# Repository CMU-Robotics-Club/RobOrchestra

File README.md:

RobOrchestra
=============

Welcome to RobOrchestra! RobOrchestra is an ongoing project in the Carnegie Mellon Robotics Club that aims to explore the creative possibilities for robotic instruments. We design, build and program robots that read music from MIDI data in order to put on musical performances. Our goal is to create a full robotic orchestra that is able to play from arrangements from standard MIDI files, and is also able to "improvise" unique polyphonic music in real time based off of music generation algorithms developed by our team.

Check out this demo video: https://drive.google.com/open?id=1UAF38HtQlL7tU6Xmdl4eHLXhHpyFQM5X

### How it works.
	
The robots, all powered by Arduinos with MIDI shields, operate via a distributed network. A laptop acts as the "conductor", transmitting MIDI siginals through the network of robots. Each robot reads the data and picks out its own part, and then plays it accordingly. We use Processing, a powerful music programming language, to control the orchestra, however it should work with nearly any MIDI software.

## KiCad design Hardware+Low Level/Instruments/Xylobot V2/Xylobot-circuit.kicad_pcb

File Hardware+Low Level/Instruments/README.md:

Instruments
===========

Each directory contains Arduino code, CAD files and documentation for each of our Robotic Instruments.

### Completed Robots
* tomBot
* snareBot
* xyloBot

### In Progress Robots
* ukuleleBot
* roboOboe
* harmonicaBot
* ViolinBot
* XyloBot V2

(Older, unused robot designs can be found in the "archives" directory.)

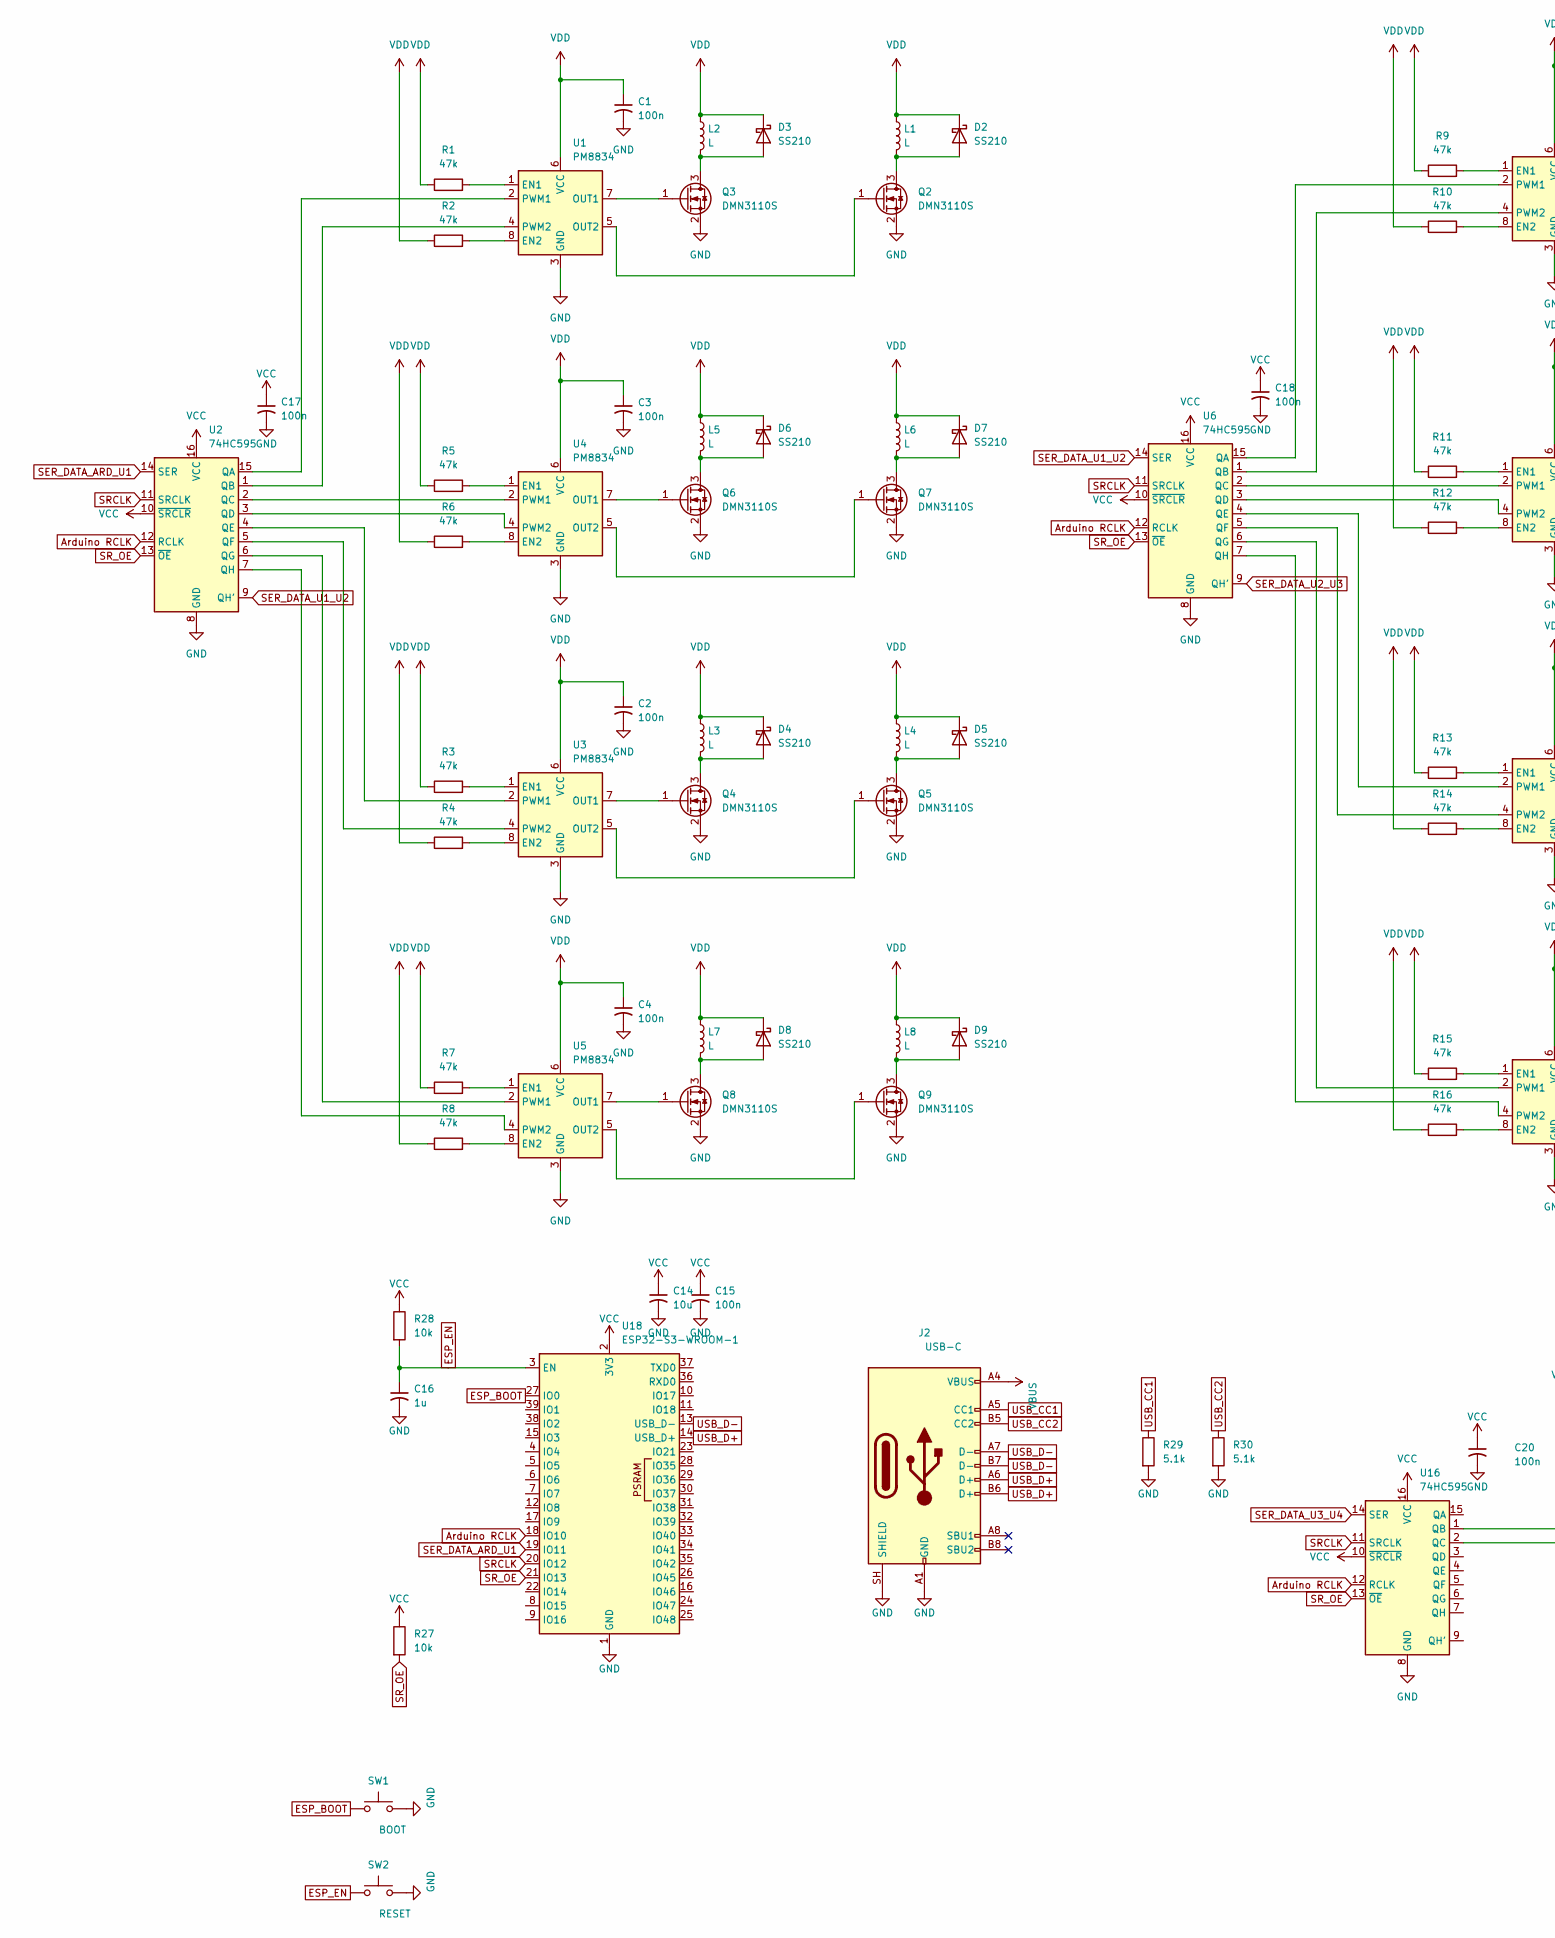
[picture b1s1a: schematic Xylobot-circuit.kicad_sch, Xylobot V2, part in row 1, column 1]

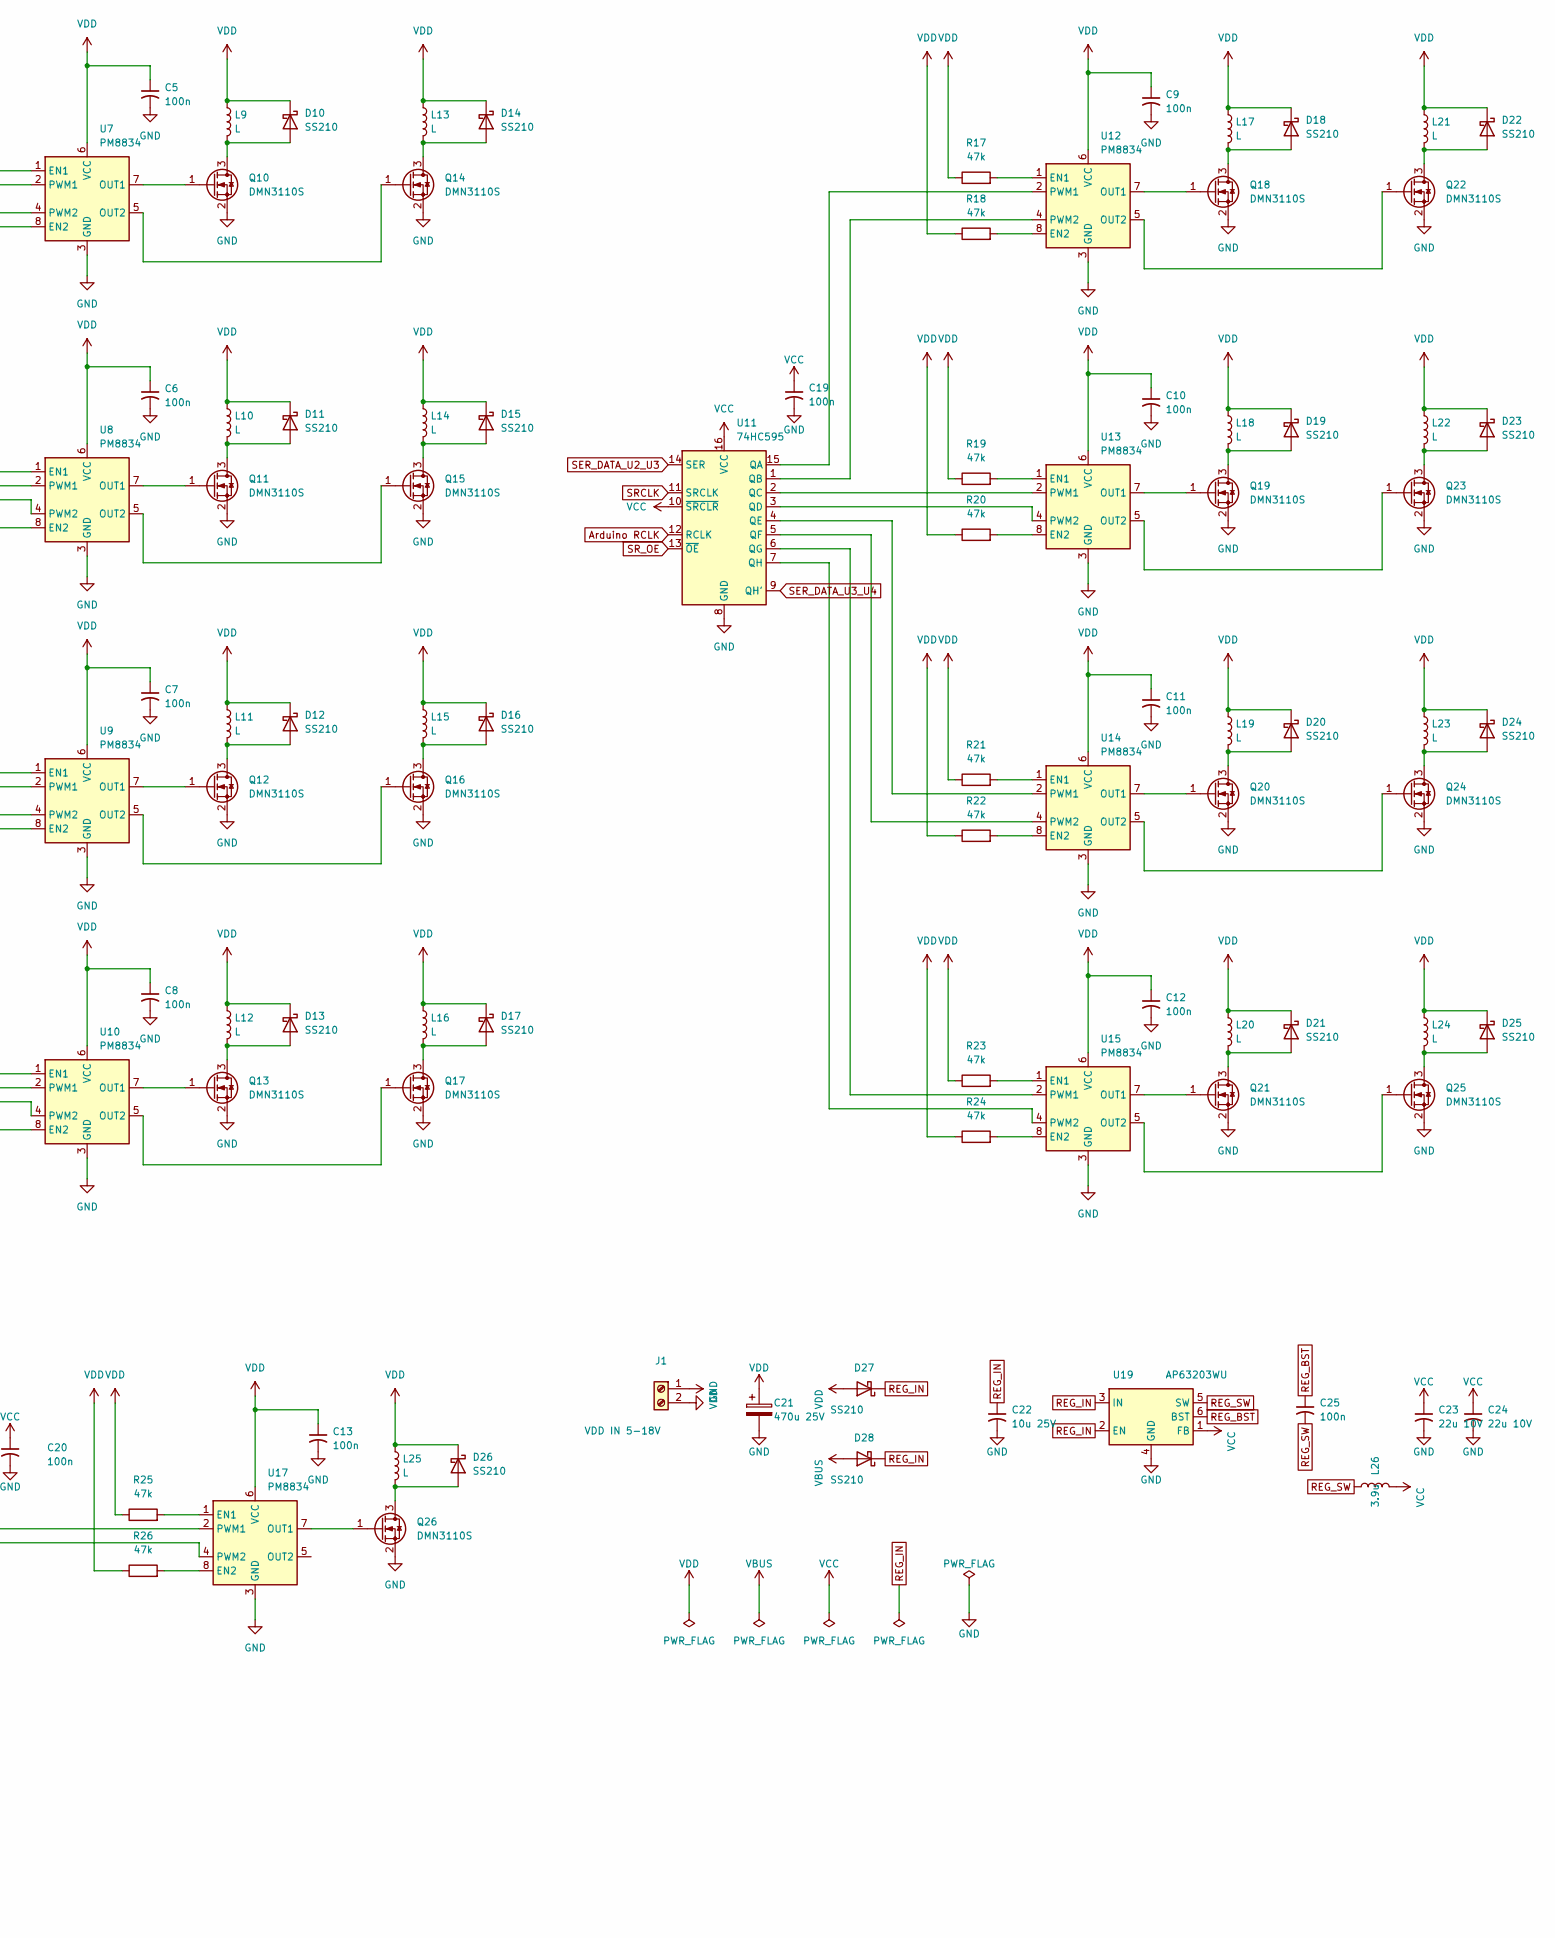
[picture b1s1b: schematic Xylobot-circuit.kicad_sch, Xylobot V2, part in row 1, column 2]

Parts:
C1, C2, C3, C4, C5, C6, C7, C8, C9, C10, C11, C12, C13, C15, C17, C18, C19, C20, C25: 100n; C_0603_1608Metric
C14: 10u; C_0805_2012Metric
C16: 1u; C_0603_1608Metric
C21: 470u 25V; CP_Radial_D10.0mm_P5.00mm
C22: 10u 25V; C_1206_3216Metric
C23, C24: 22u 10V; C_0805_2012Metric
D2, D3, D4, D5, D6, D7, D8, D9, D10, D11, D12, D13, D14, D15, D16, D17, D18, D19, D20, D21, D22, D23, D24, D25, D26, D27, D28: SS210; D_SMA
J1: VDD IN 5-18V; TerminalBlock_Phoenix_MKDS-1,5-2-5.08_1x02_P5.08mm_Horizont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
J2: USB-C; USB_C_Receptacle_HRO_TYPE-C-31-M-12
L1, L2, L3, L4, L5, L6, L7, L8, L9, L10, L11, L12, L13, L14, L15, L16, L17, L18, L19, L20, L21, L22, L23, L24, L25: L; TerminalBlock_Phoenix_MKDS-1,5-2-5.08_1x02_P5.08mm_Horizont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
L26: 3.9u; L_Bourns-SRN4018
Q2, Q3, Q4, Q5, Q6, Q7, Q8, Q9, Q10, Q11, Q12, Q13, Q14, Q15, Q16, Q17, Q18, Q19, Q20, Q21, Q22, Q23, Q24, Q25, Q26: DMN3110S; SOT-23
R1, R2, R3, R4, R5, R6, R7, R8, R9, R10, R11, R12, R13, R14, R15, R16, R17, R18, R19, R20, R21, R22, R23, R24, R25, R26: 47k; R_0603_1608Metric
R27, R28: 10k; R_0603_1608Metric
R29, R30: 5.1k; R_0603_1608Metric
SW1: BOOT; SW_PUSH_6mm
SW2: RESET; SW_PUSH_6mm
U1, U3, U4, U5, U7, U8, U9, U10, U12, U13, U14, U15, U17: PM8834; SOIC-8_3.9x4.9mm_P1.27mm
U2, U6, U11, U16: 74HC595; SOIC-16_3.9x9.9mm_P1.27mm
U18: ESP32-S3-WROOM-1
U19: AP63203WU; TSOT-23-6

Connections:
Arduino RCLK: U2.12 (RCLK), U6.12 (RCLK), U11.12 (RCLK), U16.12 (RCLK), U18.18 (IO10)
GND: C1.2, C2.2, C3.2, C4.2, C5.2, C6.2, C7.2, C8.2, C9.2, C10.2, C11.2, C12.2, C13.2, C14.2, C15.2, C16.2, C17.2, C18.2, C19.2, C20.2, C21.2, C22.2, C23.2, C24.2, J1.2, J2.A1 (GND), J2.A12 (GND), J2.B1 (GND), J2.B12 (GND), J2.SH (SHIELD), Q2.2 (S), Q3.2 (S), Q4.2 (S), Q5.2 (S), Q6.2 (S), Q7.2 (S), Q8.2 (S), Q9.2 (S), Q10.2 (S), Q11.2 (S), Q12.2 (S), Q13.2 (S), Q14.2 (S), Q15.2 (S), Q16.2 (S), Q17.2 (S), Q18.2 (S), Q19.2 (S), Q20.2 (S), Q21.2 (S), Q22.2 (S), Q23.2 (S), Q24.2 (S), Q25.2 (S), Q26.2 (S), R29.2, R30.2, SW1.2, SW2.2, U1.3 (GND), U2.8 (GND), U3.3 (GND), U4.3 (GND), U5.3 (GND), U6.8 (GND), U7.3 (GND), U8.3 (GND), U9.3 (GND), U10.3 (GND), U11.8 (GND), U12.3 (GND), U13.3 (GND), U14.3 (GND), U15.3 (GND), U16.8 (GND), U17.3 (GND), U18.1 (GND), U18.40 (GND), U18.41 (GND), U19.4 (GND)
unnamed: C22.1, D27.1 (K), D28.1 (K), U19.2 (EN), U19.3 (IN)
unnamed: C25.1, U19.6 (BST)
unnamed: C25.2, L26.1, U19.5 (SW)
unnamed: D2.2 (A), L1.2, Q2.3 (D)
unnamed: D3.2 (A), L2.2, Q3.3 (D)
unnamed: D4.2 (A), L3.2, Q4.3 (D)
unnamed: D5.2 (A), L4.2, Q5.3 (D)
unnamed: D6.2 (A), L5.2, Q6.3 (D)
unnamed: D7.2 (A), L6.2, Q7.3 (D)
unnamed: D8.2 (A), L7.2, Q8.3 (D)
unnamed: D9.2 (A), L8.2, Q9.3 (D)
unnamed: D10.2 (A), L9.2, Q10.3 (D)
unnamed: D11.2 (A), L10.2, Q11.3 (D)
unnamed: D12.2 (A), L11.2, Q12.3 (D)
unnamed: D13.2 (A), L12.2, Q13.3 (D)
unnamed: D14.2 (A), L13.2, Q14.3 (D)
unnamed: D15.2 (A), L14.2, Q15.3 (D)
unnamed: D16.2 (A), L15.2, Q16.3 (D)
unnamed: D17.2 (A), L16.2, Q17.3 (D)
unnamed: D18.2 (A), L17.2, Q18.3 (D)
unnamed: D19.2 (A), L18.2, Q19.3 (D)
unnamed: D20.2 (A), L19.2, Q20.3 (D)
unnamed: D21.2 (A), L20.2, Q21.3 (D)
unnamed: D22.2 (A), L21.2, Q22.3 (D)
unnamed: D23.2 (A), L22.2, Q23.3 (D)
unnamed: D24.2 (A), L23.2, Q24.3 (D)
unnamed: D25.2 (A), L24.2, Q25.3 (D)
unnamed: D26.2 (A), L25.2, Q26.3 (D)
unnamed: D28.2 (A), J2.A4 (VBUS), J2.A9 (VBUS), J2.B4 (VBUS), J2.B9 (VBUS)
unnamed: J2.A5 (CC1), R29.1
unnamed: J2.A6 (D+), J2.B6 (D+), U18.14 (USB_D+)
unnamed: J2.A7 (D-), J2.B7 (D-), U18.13 (USB_D-)
unnamed: J2.B5 (CC2), R30.1
unnamed: Q2.1 (G), U1.5 (OUT2)
unnamed: Q3.1 (G), U1.7 (OUT1)
unnamed: Q4.1 (G), U3.7 (OUT1)
unnamed: Q5.1 (G), U3.5 (OUT2)
unnamed: Q6.1 (G), U4.7 (OUT1)
unnamed: Q7.1 (G), U4.5 (OUT2)
unnamed: Q8.1 (G), U5.7 (OUT1)
unnamed: Q9.1 (G), U5.5 (OUT2)
unnamed: Q10.1 (G), U7.7 (OUT1)
unnamed: Q11.1 (G), U8.7 (OUT1)
unnamed: Q12.1 (G), U9.7 (OUT1)
unnamed: Q13.1 (G), U10.7 (OUT1)
unnamed: Q14.1 (G), U7.5 (OUT2)
unnamed: Q15.1 (G), U8.5 (OUT2)
unnamed: Q16.1 (G), U9.5 (OUT2)
unnamed: Q17.1 (G), U10.5 (OUT2)
unnamed: Q18.1 (G), U12.7 (OUT1)
unnamed: Q19.1 (G), U13.7 (OUT1)
unnamed: Q20.1 (G), U14.7 (OUT1)
unnamed: Q21.1 (G), U15.7 (OUT1)
unnamed: Q22.1 (G), U12.5 (OUT2)
unnamed: Q23.1 (G), U13.5 (OUT2)
unnamed: Q24.1 (G), U14.5 (OUT2)
unnamed: Q25.1 (G), U15.5 (OUT2)
unnamed: Q26.1 (G), U17.7 (OUT1)
unnamed: SW1.1, U18.27 (IO0)
unnamed: R1.2, U1.1 (EN1)
unnamed: R2.2, U1.8 (EN2)
unnamed: U1.2 (PWM1), U2.15 (QA)
unnamed: U1.4 (PWM2), U2.1 (QB)
unnamed: U2.2 (QC), U4.2 (PWM1)
unnamed: U2.3 (QD), U4.4 (PWM2)
unnamed: U2.4 (QE), U3.2 (PWM1)
unnamed: U2.5 (QF), U3.4 (PWM2)
unnamed: U2.6 (QG), U5.2 (PWM1)
unnamed: U2.7 (QH), U5.4 (PWM2)
unnamed: R3.2, U3.1 (EN1)
unnamed: R4.2, U3.8 (EN2)
unnamed: R5.2, U4.1 (EN1)
unnamed: R6.2, U4.8 (EN2)
unnamed: R7.2, U5.1 (EN1)
unnamed: R8.2, U5.8 (EN2)
unnamed: U6.15 (QA), U7.2 (PWM1)
unnamed: U6.1 (QB), U7.4 (PWM2)
unnamed: U6.2 (QC), U8.2 (PWM1)
unnamed: U6.3 (QD), U8.4 (PWM2)
unnamed: U6.4 (QE), U9.2 (PWM1)
unnamed: U6.5 (QF), U9.4 (PWM2)
unnamed: R9.2, U7.1 (EN1)
unnamed: R10.2, U7.8 (EN2)
unnamed: R11.2, U8.1 (EN1)
unnamed: R12.2, U8.8 (EN2)
unnamed: R13.2, U9.1 (EN1)
unnamed: R14.2, U9.8 (EN2)
unnamed: R15.2, U10.1 (EN1)
unnamed: R16.2, U10.8 (EN2)
unnamed: U6.6 (QG), U10.2 (PWM1)
unnamed: U6.7 (QH), U10.4 (PWM2)
unnamed: U11.15 (QA), U12.2 (PWM1)
unnamed: U11.1 (QB), U12.4 (PWM2)
unnamed: U11.2 (QC), U13.2 (PWM1)
unnamed: U11.3 (QD), U13.4 (PWM2)
unnamed: U11.4 (QE), U14.2 (PWM1)
unnamed: U11.5 (QF), U14.4 (PWM2)
unnamed: U11.6 (QG), U15.2 (PWM1)
unnamed: U11.7 (QH), U15.4 (PWM2)
unnamed: R17.2, U12.1 (EN1)
unnamed: R18.2, U12.8 (EN2)
unnamed: R19.2, U13.1 (EN1)
unnamed: R20.2, U13.8 (EN2)
unnamed: R21.2, U14.1 (EN1)
unnamed: R22.2, U14.8 (EN2)
unnamed: R23.2, U15.1 (EN1)
unnamed: R24.2, U15.8 (EN2)
unnamed: U16.1 (QB), U17.2 (PWM1)
unnamed: U16.2 (QC), U17.4 (PWM2)
unnamed: R25.2, U17.1 (EN1)
unnamed: R26.2, U17.8 (EN2)
unnamed: C16.1, R28.2, SW2.1, U18.3 (EN)
SER_DATA_ARD_U1: U2.14 (SER), U18.19 (IO11)
SER_DATA_U1_U2: U2.9 (QH'), U6.14 (SER)
SER_DATA_U2_U3: U6.9 (QH'), U11.14 (SER)
SER_DATA_U3_U4: U11.9 (QH'), U16.14 (SER)
SRCLK: U2.11 (SRCLK), U6.11 (SRCLK), U11.11 (SRCLK), U16.11 (SRCLK), U18.20 (IO12)
SR_OE: R27.2, U2.13 (~OE), U6.13 (~OE), U11.13 (~OE), U16.13 (~OE), U18.21 (IO13)
VCC: C14.1, C15.1, C17.1, C18.1, C19.1, C20.1, C23.1, C24.1, L26.2, R27.1, R28.1, U2.10 (~SRCLR), U2.16 (VCC), U6.10 (~SRCLR), U6.16 (VCC), U11.10 (~SRCLR), U11.16 (VCC), U16.10 (~SRCLR), U16.16 (VCC), U18.2 (3V3), U19.1 (FB)
VDD: C1.1, C2.1, C3.1, C4.1, C5.1, C6.1, C7.1, C8.1, C9.1, C10.1, C11.1, C12.1, C13.1, C21.1, D2.1 (K), D3.1 (K), D4.1 (K), D5.1 (K), D6.1 (K), D7.1 (K), D8.1 (K), D9.1 (K), D10.1 (K), D11.1 (K), D12.1 (K), D13.1 (K), D14.1 (K), D15.1 (K), D16.1 (K), D17.1 (K), D18.1 (K), D19.1 (K), D20.1 (K), D21.1 (K), D22.1 (K), D23.1 (K), D24.1 (K), D25.1 (K), D26.1 (K), D27.2 (A), J1.1, L1.1, L2.1, L3.1, L4.1, L5.1, L6.1, L7.1, L8.1, L9.1, L10.1, L11.1, L12.1, L13.1, L14.1, L15.1, L16.1, L17.1, L18.1, L19.1, L20.1, L21.1, L22.1, L23.1, L24.1, L25.1, R1.1, R2.1, R3.1, R4.1, R5.1, R6.1, R7.1, R8.1, R9.1, R10.1, R11.1, R12.1, R13.1, R14.1, R15.1, R16.1, R17.1, R18.1, R19.1, R20.1, R21.1, R22.1, R23.1, R24.1, R25.1, R26.1, U1.6 (VCC), U3.6 (VCC), U4.6 (VCC), U5.6 (VCC), U7.6 (VCC), U8.6 (VCC), U9.6 (VCC), U10.6 (VCC), U12.6 (VCC), U13.6 (VCC), U14.6 (VCC), U15.6 (VCC), U17.6 (VCC)

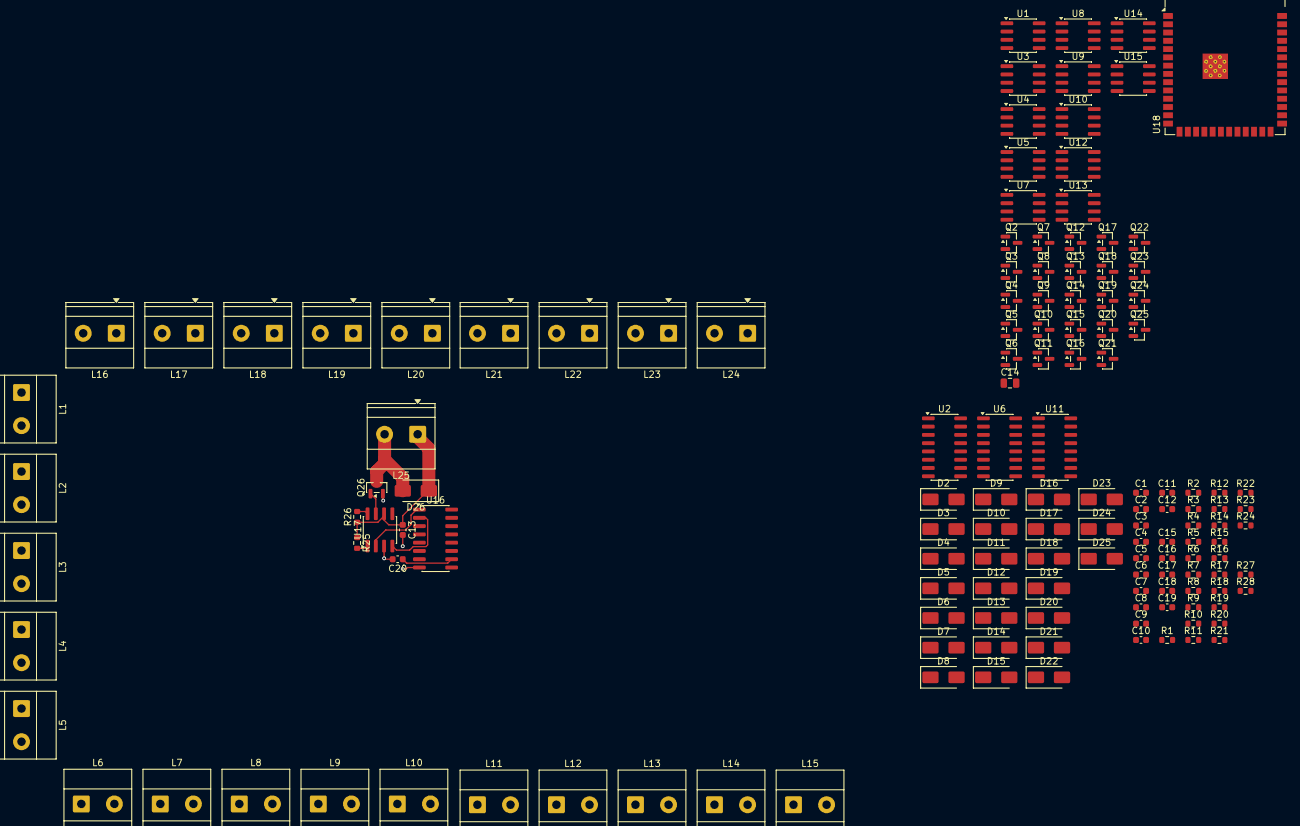
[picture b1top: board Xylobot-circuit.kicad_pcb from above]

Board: 2 copper layers, 141 parts (0 on the bottom side), 113 nets.

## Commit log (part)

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2017-11-13 Removed Redundant Notes
    There were redundant notes. They are now gone. Celebrate!
2017-11-13 Rhythm Updates
2017-11-13 BASIC MARKOV DOESNT COMPILE - TEMPORARY MAJOR CHANGES
    Changes are modifying all of basic markov, chorddetection, and playnotethread to take int arrays
2017-11-27 Removed unnecessary files in BasicMarkov
2017-11-27 Partially implemented proper chord playing in PlayNoteThread
2017-11-27 Fixed some flaws in chord detection with making assumptions based on order of notes inputted
2017-11-28 Made Chord Detection slightly more accurate when returning basic major and minor chords
2017-12-18 Messing around with having chords gradually decrescendo and jump back up to full volume occasionally, rather than just playing 10% of the chords chosen randomly. Seems okay to me (less like monkey ba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
2018-01-22 Updated slider range on interactive demo
2018-01-22 Actually committing the dominant 7th fix...
2018-01-29 Cleaned up xylobot low level. To do: Discretize time and teach the low-level code to go back in time on receiving MIDI messages.
2018-02-19 Updated xylobot code, moved BasicMarkov from Test Code to Music Generation Algorithms, renamed it ChordMarkov.
2018-02-19 Old Xylobot code retrieved, new Xylobot code cleaned up
2018-03-05 Updated pin numbers in Arduino Xylobot code
2018-03-05 Xylobot code now timing each solenoid independently. All chords now not simultaneous, but the time discrepancies are smaller. Might be an improvement? Still need to clean up unused code though...
2018-03-19 Made the state length its own variable in the Markov chain code.
2018-03-19 Got the Ukelele Arduino code to compile (I hope it's the right file, and I'm pretty sure it compiles now and didn't before), but I'm not great with C, so I'm not sure it works at all. A good chunk of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
2018-03-26 Updated snarebot code
2018-03-26 CounterPointFirstSpecies and Generate added to CounterPointFirstSpecies Folder
2018-03-26 Added RULEFILTER and CHORDGETTER functions
2018-04-02 Add files via upload
    Made interactive demo melody more linear.
2018-04-02 Tested bassLineGen and added Voice class (not sure if we will use this or not but we'll see lol)
2018-04-09 Add files via upload
    Added second line
2018-04-09 More playign with the score stuff. More comments.
2018-04-09 Added score to Generate
2018-04-09 NAIVE MELODY LINE
2018-04-16 Revert "Changed solenoid pin numbers. Code not compiling; something about arrays not being correct..."
    This reverts commit 65ad4aaf9797b1c8c7a006cf14857be444ede811.
2018-04-16 Pins should hopefully be correct?
2018-04-16 Removed the other Ukelelebot code file
2018-04-16 Add files via upload
    Added melody and harmony button labels
2018-04-16 fixed everything
2018-04-23 Added second species file and fixed resolution of first species outputted score
2018-04-30 Ukelele code changes
2018-10-29 Changed OpenCV folder to Interaction
2018-11-01 Added HSVColorTracking Example from OpenCV Library
    So Processing's version of OpenCV is really old. We don't have fast circle tracking algorithms like Hough Circle Transform. Instead we'll have to either track color, blobs, or cascades. I found an ex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
2018-11-05 Put HSV stuff in CV_Interaction
2018-11-12 magnitude
    added double get_magnitude to point vector class
2018-11-19 Added more accuracy to opencv
2018-11-26 Added Ukulele test code
2019-01-25 Various changes. Got ChordMarkov to play Despacito
2019-01-25 Revert "no message"
    This reverts commit c9e763ef3822c5faf165526e0a1690b5cc227487.
2019-01-28 Finished resolving merge conflicts. Hopefully stuff still works; if not, revert.
2019-02-13 Uploaded in-progress CAD parts to github
2019-02-19 Messed around with Markov_with_CV; still not picking up the object correctly.
2019-02-25 Moved blur before display so when we grab a color, we grab the blurred color. Then lowered thresholds to filter more background noise.
2019-02-28 Folder Reordering
    Cleaned up the repo. Still contains file repetitions, but should be more organized now.
2019-03-01 Added SimpleSynth 64-bit port
    SimpleSynth hasn't been updated since 2009, and we probably want to keep using it. Recompiled the source code for macOS 10.14 and fixed MOST deprecation issues. Still not a 100% future proof, but sho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
    P.S. I checked and we are permitted to distribute copies of the program (read: about simplesynth, in app).
2019-03-28 Xylobot code cleanup. Should work (tested on RoboOboe, plus partial testing on Xylobot) but revert if something weird breaks
2019-04-03 added CV template
2019-04-29 Added some test code and songs for single-note instruments (mostly for testing Robo-Oboe, but someone might find it useful later). We really should reorganize these folders, though; somehow the relev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
2019-05-20 Added RoboOboe TODOs
2019-09-28 folder rename
2019-09-30 linear actuator
2019-09-30 added external components
2019-10-01 Update README.md
    Updated contact info, meeting times, and instruments in the orch
2019-10-10 putting in parts
2019-10-14 inner servo housing part CAD file
2019-10-14 Add outer finger files via upload
2019-10-14 Create alice-servo-test.ino
    Created Alice's Arduino test file to work with servos
2019-10-14 added inner servo housings to general assembly
2019-10-16 Location
    getVector() just points to an data struct that contains x,y,dx,dy. It's in Arduino, but I think moving it into processing shouldn't take that much time.
2019-10-16 Added file reading code but checking validity of string doesn't work yet
2019-10-16 Fixed bug where snare/tom msgs here being played by xylobot (causing c# note on). Now xylobot only accepts channel1 messages
2019-10-21 putting components into main assembly
2019-10-21 Putting everything into assembly
2019-10-21 steven's components
2019-10-21 manufacturing files
2019-10-21 assembly update
2019-10-23 fixed matlab
2019-11-04 more CAD development
2019-11-06 Added I'm Yours MuseScore files
    And added Sharon's MATLAB test
2019-11-11 small update
2019-11-11 Pick Holder CAD
2019-11-13 Added The Scientist
2019-11-13 shape of you
2019-11-13 added payphone
2019-11-15 servo holder adjustment
2019-11-20 Read more data from pixy
2019-12-02 linear actuator code
2020-02-05 Updated readme with video link
2020-02-21 Add files via upload
    Added comments for frequently-changed variables. The ultimate goal is to be able to run this from the command line, with those variables as inputs.
2020-03-18 Started work on a (buggy) Markov chain for chords
    Sorry if I'm stepping on someone's toes here, but I was travelling and bored.
    I've started implmenting the chord-based Markov chain in chordHMM. It's not a full HMM yet, as it doesn't do anything with the melody line. It also seems to have issues identifying chords. I'll see i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
2020-03-19 Fixed Edge Cases
    First chord in certain files (like "I'm Yours") is shorter by about 100 ticks than later chords, but that's the only weirdness I'm seeing now.
    If I'm bored with a large chunk of time, I'll start working on that melody reader, but I don't know if/when I'll get to that. If anyone wants to take over from here, feel free (but let me know so I d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
2020-11-01 Renamed folder
    Trying to fix errors for people cloning
2020-11-08 Added MultiSongChordMarkov
    Takes two songs, randomly transitions within/between them.
    Next steps:
    Use multiple songs?
    If an attempted transition fails, keep trying on all future notes until it works?
    (NOTE: Changed the State class so length==delay to make this work on Sam's demo songs, might need to look into this)
2020-11-22 Added Wagon Wheel midi
2020-11-22 Changed key of Wagon Wheel to C
2020-11-22 Modified multisong input to take in any number of inputs
    Bug - song index isn't incrementing properly
2020-12-06 Corrected MIDI files for Don't Stop Believing and With or Without You
2021-03-28 test noteToPos
2021-04-04 merged test code with wiring for ukueleCtrl
2021-04-11 Theremin code to output a note based on the position of an object using the Pixy2
2021-05-02 added calibration and all 4 strings move at same time
2021-10-01 Cleanup on MultiSongChordMarkov
2021-10-08 Added serial to MIDI example
    chromaticTest sends desired pitches over serial.
    playMIDI reads serial messages and plays the corresponding notes.
2021-10-15 Comments for theremin integration
2021-10-29 Created ML music generation folder and jupyter notebook
2021-11-12 created handbell dxf for laser cutting
2021-11-19 added spaces
2021-11-19 while loop
2021-11-19 Completed working virtual theremin that changes pitch and volume simultaneously
2021-12-03 Moved conducting code to conducting folder
2023-01-05 Added PlaySong to play a MIDI file
    PlaySong plays all tracks of a MIDI file; Markov code with really long state length only plays one track plus maybe chords.
    It's still a bit hacky (I start up a bunch of threads and hope they don't interfere with each other or get out of sync), and ideally we'd find something that lets us play stuff through MuseScore dire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
2023-02-17 Adaptive threshold bang-bang for linear actuator
    Also some messing around from our last demo
2023-02-23 Multi actuator
2023-10-12 add playMIDIconduct
2023-10-27 interactive demo conducting
2023-12-01 add HMM & related files
2024-02-09 MIDI->python
2024-02-16 Remove annoying prints
2024-02-23 Retune snarebot
2024-03-01 Starting playSong2
    Not working yet. Also some tweaks from expo
2024-03-15 Transformer tests
    I think we're misindexing in play (and maybe in training), but not sure how to fix
2024-03-15 transformer fixes
2024-04-05 playSong2 fix with processing 4, FFT/PitchDetector
2024-04-12 amplitude detector
2024-04-12 Merge
2024-04-19 Basic localization code
2024-05-02 Updates from last meeting
2024-05-03 add position to localizer2D
2024-05-03 Somewhat working demo!
2024-08-26 Interactive Demo Fixed?
    surface.setSize() doesn't change Processing responsive area anymore? Super weird bug
2024-09-03 Reimplemented FFT localizer with matrix library
    Mostly not vectorized yet, so probably not much faster than what we had, but seems to be working?
    Seems to be jumping octaves in playback, though - I'll have to check on that at some point...
2024-09-10 fixes
2024-09-17 FFT Localizer Now Faster
2024-10-08 Update fftLocalizer2DMatrixFast.pde
    General code cleanup - removed big chunks of commented code, removed unneeded inputs, added some comments on whatever was left. Also set up the main code to handle a rhythmPattern that'll come out of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
2024-10-22 min/max bpm -> min/max ms per measure
2024-10-22 NoteArray fixes
2024-10-22 buggy
2024-10-22 Cleanup and have resample not insert 0s
2024-10-29 Update fftLocalizer2DMatrixFast.pde
    Parameter tuning
2024-11-05 Add MIDImaker
    Still need autocorrelate code to identify rhythm line
2024-11-05 Working?
2024-11-12 Reduce empty measures at start of WWRY
2024-11-12 More cleanup
2024-11-26 Add Volume Tuning Program
2024-12-03 Non-repeating rhythm line
2025-01-23 Non repeated FFT
2025-02-06 filter semi-fix
2025-02-27 frequency detect fixes
2025-02-28 multiple pitch detect
2025-04-10 Fix end-of-measure?
2025-04-10 Add same-length track fix to the versions we'll be using
2025-04-10 archive intermediate versions of fft
2025-04-10 fft with markov
2025-04-10 note array extra track for conducting
2025-04-11 HOPEFULLY NOT BROKEN?
    Blind-copying tempoGaussMat update to all current code files. If something ends up broken in the near future, it's probably related to this
2025-04-17 Boolean toggles for notes/conducting
    Also some general parameter cleanup
2025-04-17 Read double-pattern 6/8 correctly
2025-04-17 call & response tests
2025-04-25 Needs more testing
    Normalized beatProbsArr correctly I hope. TODO test with oboe or something. Seems to mostly stick to whatever transposition it starts with, but it's hard to tell if it's correct without known notes. 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
2025-05-01 pitchdetect changes
2025-05-01 Update fftLocalizerTransposeDavidTest.pde
    Twinkle twinkle settings for oboe in quiet room, apparently
2025-09-14 Rename
2026-03-08 Add second MidiBus to interactive demos
    Idea is to have one MidiBus point to Xylobot and the other point to the Bluetooth stuff for the drums
2026-03-09 Quick DrumBot Commit
2026-03-12 changed drumbot md
2026-03-14 bettered latency and fixed mirrored weirdness
